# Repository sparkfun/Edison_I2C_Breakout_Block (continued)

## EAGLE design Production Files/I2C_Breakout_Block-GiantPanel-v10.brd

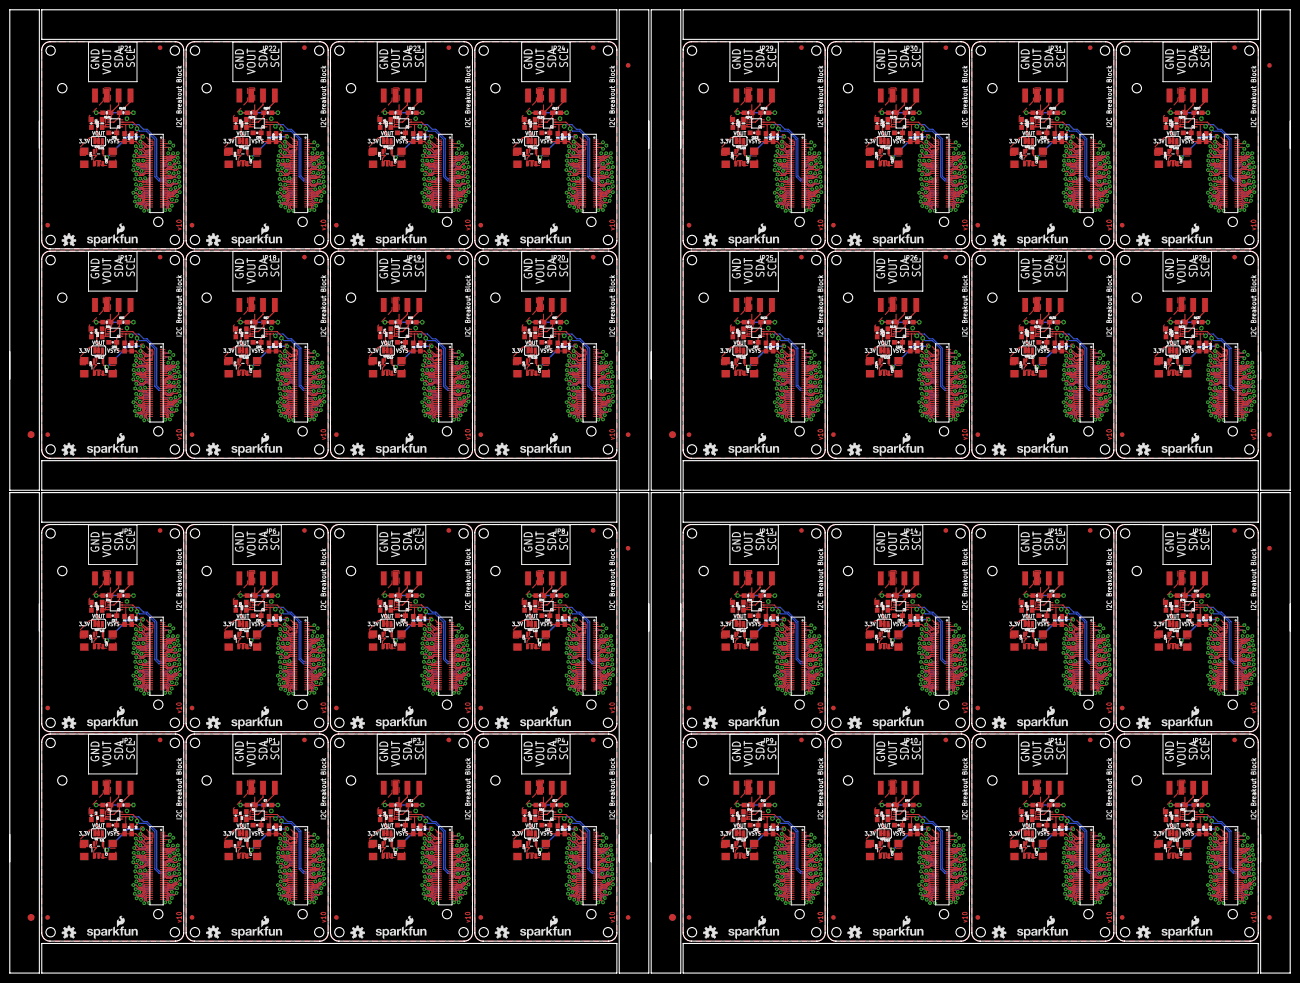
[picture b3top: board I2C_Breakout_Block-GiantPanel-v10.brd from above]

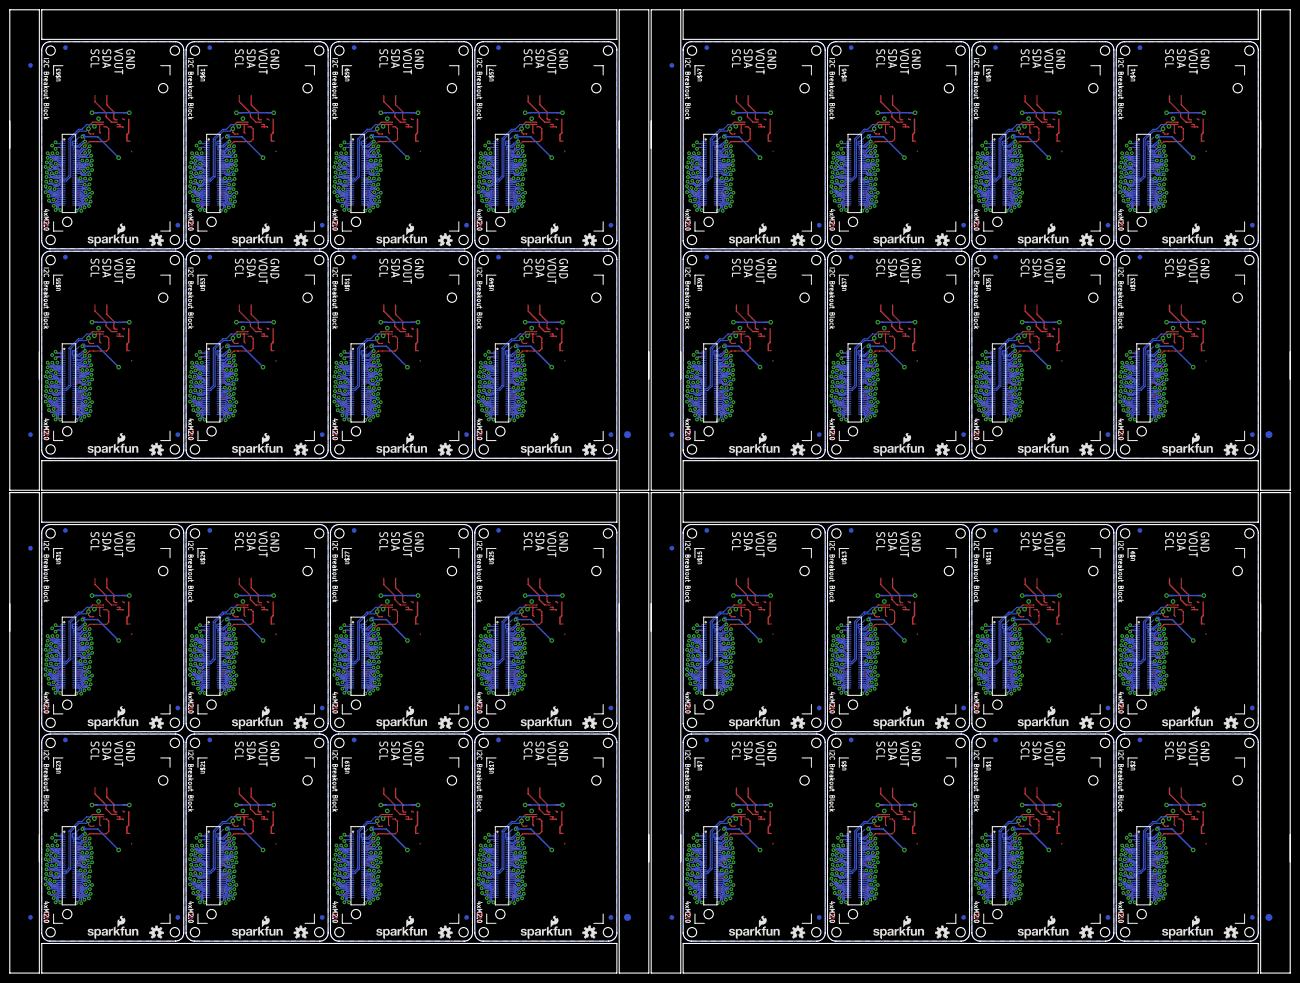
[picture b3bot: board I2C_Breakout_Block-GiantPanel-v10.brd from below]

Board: 2 copper layers, 274.8 x 206.8 mm, 760 parts (204 on the bottom side), 2016 nets.

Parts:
C1, C2, C5, C6, C9, C10, C13, C14, C17, C18, C21, C22, C25, C26, C29, C30, C33, C34, C37, C38, C41, C42, C45, C46, C49, C50, C53, C54, C57, C58, C61, C62, C65, C66, C69, C70, C73, C74, C77, C78, C81, C82, C85, C86, C89, C90, C93, C94, C97, C98, C101, C102, C105, C106, C109, C110, C113, C114, C117, C118, C121, C122, C125, C126: 0.1uF; 0603-CAP
C3, C4, C7, C8, C11, C12, C15, C16, C19, C20, C23, C24, C27, C28, C31, C32, C35, C36, C39, C40, C43, C44, C47, C48, C51, C52, C55, C56, C59, C60, C63, C64, C67, C68, C71, C72, C75, C76, C79, C80, C83, C84, C87, C88, C91, C92, C95, C96, C99, C100, C103, C104, C107, C108, C111, C112, C115, C116, C119, C120, C123, C124, C127, C128: 10uF; 1206
E$1, E$2, E$9, E$10, E$15, E$16, E$21, E$22: FIDUCIAL-1.5X3
E$3, E$4, E$5, E$6, E$7, E$8, E$11, E$12, E$13, E$14, E$17, E$18, E$19, E$20, E$23, E$24: FIDUCIAL-1X2
FID1, FID2, FID3, FID4, FID5, FID6, FID7, FID8, FID9, FID10, FID11, FID12, FID13, FID14, FID15, FID16, FID17, FID18, FID19, FID20, FID21, FID22, FID23, FID24, FID25, FID26, FID27, FID28, FID29, FID30, FID31, FID32, FID33, FID34, FID35, FID36, FID37, FID38, FID39, FID40, FID41, FID42, FID43, FID44, FID45, FID46, FID47, FID48, FID49, FID50, FID51, FID52, FID53, FID54, FID55, FID56, FID57, FID58, FID59, FID60, FID61, FID62, FID63, FID64, FID65, FID66, FID67, FID68, FID69, FID70, FID71, FID72, FID73, FID74, FID75, FID76, FID77, FID78, FID79, FID80, FID81, FID82, FID83, FID84, FID85, FID86, FID87, FID88, FID89, FID90, FID91, FID92, FID93, FID94, FID95, FID96, FID97, FID98, FID99, FID100, FID101, FID102, FID103, FID104, FID105, FID106, FID107, FID108, FID109, FID110, FID111, FID112, FID113, FID114, FID115, FID116, FID117, FID118, FID119, FID120, FID121, FID122, FID123, FID124, FID125, FID126, FID127, FID128: FIDUCIAL1X2; FIDUCIAL-1X2
JP1, JP2, JP3, JP4, JP5, JP6, JP7, JP8, JP9, JP10, JP11, JP12, JP13, JP14, JP15, JP16, JP17, JP18, JP19, JP20, JP21, JP22, JP23, JP24, JP25, JP26, JP27, JP28, JP29, JP30, JP31, JP32: 1X04_SMD_RA_FEMALE
LOGO1, LOGO3, LOGO6, LOGO7, LOGO10, LOGO11, LOGO14, LOGO15, LOGO18, LOGO19, LOGO22, LOGO23, LOGO26, LOGO27, LOGO30, LOGO31, LOGO34, LOGO35, LOGO38, LOGO39, LOGO42, LOGO43, LOGO46, LOGO47, LOGO50, LOGO51, LOGO54, LOGO55, LOGO58, LOGO59, LOGO62, LOGO63, LOGO66, LOGO67, LOGO70, LOGO71, LOGO74, LOGO75, LOGO78, LOGO79, LOGO82, LOGO83, LOGO86, LOGO87, LOGO90, LOGO91, LOGO94, LOGO95, LOGO98, LOGO99, LOGO102, LOGO103, LOGO106, LOGO107, LOGO110, LOGO111, LOGO114, LOGO115, LOGO118, LOGO119, LOGO122, LOGO123, LOGO126, LOGO127: SFE_LOGO_NAME_FLAME.1_INCH; SFE_LOGO_NAME_FLAME_.1
LOGO2, LOGO4, LOGO5, LOGO8, LOGO9, LOGO12, LOGO13, LOGO16, LOGO17, LOGO20, LOGO21, LOGO24, LOGO25, LOGO28, LOGO29, LOGO32, LOGO33, LOGO36, LOGO37, LOGO40, LOGO41, LOGO44, LOGO45, LOGO48, LOGO49, LOGO52, LOGO53, LOGO56, LOGO57, LOGO60, LOGO61, LOGO64, LOGO65, LOGO68, LOGO69, LOGO72, LOGO73, LOGO76, LOGO77, LOGO80, LOGO81, LOGO84, LOGO85, LOGO88, LOGO89, LOGO92, LOGO93, LOGO96, LOGO97, LOGO100, LOGO101, LOGO104, LOGO105, LOGO108, LOGO109, LOGO112, LOGO113, LOGO116, LOGO117, LOGO120, LOGO121, LOGO124, LOGO125, LOGO128: OSHW-LOGOS; OSHW-LOGO-S
R1, R2, R6, R7, R11, R12, R16, R17, R21, R22, R26, R27, R31, R32, R36, R37, R41, R42, R46, R47, R51, R52, R56, R57, R61, R62, R66, R67, R71, R72, R76, R77, R81, R82, R86, R87, R91, R92, R96, R97, R101, R102, R106, R107, R111, R112, R116, R117, R121, R122, R126, R127, R131, R132, R136, R137, R141, R142, R146, R147, R151, R152, R156, R157: 10K; 0603-RES
R3, R8, R13, R18, R23, R28, R33, R38, R43, R48, R53, R58, R63, R68, R73, R78, R83, R88, R93, R98, R103, R108, R113, R118, R123, R128, R133, R138, R143, R148, R153, R158: 200k; 0603-RES
R4, R5, R9, R10, R14, R15, R19, R20, R24, R25, R29, R30, R34, R35, R39, R40, R44, R45, R49, R50, R54, R55, R59, R60, R64, R65, R69, R70, R74, R75, R79, R80, R84, R85, R89, R90, R94, R95, R99, R100, R104, R105, R109, R110, R114, R115, R119, R120, R124, R125, R129, R130, R134, R135, R139, R140, R144, R145, R149, R150, R154, R155, R159, R160: DNP; 0603-RES
SJ1, SJ2, SJ3, SJ4, SJ5, SJ6, SJ7, SJ8, SJ9, SJ10, SJ11, SJ12, SJ13, SJ14, SJ15, SJ16, SJ17, SJ18, SJ19, SJ20, SJ21, SJ22, SJ23, SJ24, SJ25, SJ26, SJ27, SJ28, SJ29, SJ30, SJ31, SJ32: Power Select; PAD-JUMPER-3-2OF3_NC_BY_TRACE_YES_SILK_FULL_BOX
U1, U4, U6, U8, U10, U12, U14, U16, U18, U20, U22, U24, U26, U28, U30, U32, U34, U36, U38, U40, U42, U44, U46, U48, U50, U52, U54, U56, U58, U60, U62, U64: MIC5205; SOT23-5
U2, U3, U5, U7, U9, U11, U13, U15, U17, U19, U21, U23, U25, U27, U29, U31, U33, U35, U37, U39, U41, U43, U45, U47, U49, U51, U53, U55, U57, U59, U61, U63: PCA9306; PCA9306DC-1:1
U$1, U$2, U$5, U$7, U$9, U$11, U$13, U$15, U$17, U$19, U$21, U$23, U$25, U$27, U$29, U$31, U$33, U$35, U$37, U$39, U$41, U$43, U$45, U$47, U$49, U$51, U$53, U$55, U$57, U$59, U$61, U$63: EDISON_CONNECTOR_FULLMOUNTING_HOLES; EDISON_DAUGHTER
U$3, U$4, U$6, U$8, U$10, U$12, U$14, U$16, U$18, U$20, U$22, U$24, U$26, U$28, U$30, U$32, U$34, U$36, U$38, U$40, U$42, U$44, U$46, U$48, U$50, U$52, U$54, U$56, U$58, U$60, U$62, U$64: EDISON_CONNECTOR_FULLHEADER; DF40C-70DP-0.4(51)

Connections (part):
1.8V: C1.1, R4.2, R5.2, U2.1, U$2.12, U$3.12
1.8V1: C5.1, R9.2, R10.2, U3.1, U$1.12, U$4.12
1.8V2: C9.1, R14.2, R15.2, U5.1, U$5.12, U$6.12
1.8V3: C13.1, R19.2, R20.2, U7.1, U$7.12, U$8.12
1.8V4: C17.1, R24.2, R25.2, U9.1, U$9.12, U$10.12
1.8V5: C21.1, R29.2, R30.2, U11.1, U$11.12, U$12.12
1.8V6: C25.1, R34.2, R35.2, U13.1, U$13.12, U$14.12
1.8V7: C29.1, R39.2, R40.2, U15.1, U$15.12, U$16.12
1.8V8: C33.1, R44.2, R45.2, U17.1, U$17.12, U$18.12
1.8V9: C37.1, R49.2, R50.2, U19.1, U$19.12, U$20.12
1.8V10: C41.1, R54.2, R55.2, U21.1, U$21.12, U$22.12
1.8V11: C45.1, R59.2, R60.2, U23.1, U$23.12, U$24.12
1.8V12: C49.1, R64.2, R65.2, U25.1, U$25.12, U$26.12
1.8V13: C53.1, R69.2, R70.2, U27.1, U$27.12, U$28.12
1.8V14: C57.1, R74.2, R75.2, U29.1, U$29.12, U$30.12
1.8V15: C61.1, R79.2, R80.2, U31.1, U$31.12, U$32.12
1.8V16: C65.1, R84.2, R85.2, U33.1, U$33.12, U$34.12
1.8V17: C69.1, R89.2, R90.2, U35.1, U$35.12, U$36.12
1.8V18: C73.1, R94.2, R95.2, U37.1, U$37.12, U$38.12
1.8V19: C77.1, R99.2, R100.2, U39.1, U$39.12, U$40.12
1.8V20: C81.1, R104.2, R105.2, U41.1, U$41.12, U$42.12
1.8V21: C85.1, R109.2, R110.2, U43.1, U$43.12, U$44.12
1.8V22: C89.1, R114.2, R115.2, U45.1, U$45.12, U$46.12
1.8V23: C93.1, R119.2, R120.2, U47.1, U$47.12, U$48.12
1.8V24: C97.1, R124.2, R125.2, U49.1, U$49.12, U$50.12
1.8V25: C101.1, R129.2, R130.2, U51.1, U$51.12, U$52.12
1.8V26: C105.1, R134.2, R135.2, U53.1, U$53.12, U$54.12
1.8V27: C109.1, R139.2, R140.2, U55.1, U$55.12, U$56.12
1.8V28: C113.1, R144.2, R145.2, U57.1, U$57.12, U$58.12
1.8V29: C117.1, R149.2, R150.2, U59.1, U$59.12, U$60.12
1.8V30: C121.1, R154.2, R155.2, U61.1, U$61.12, U$62.12
1.8V31: C125.1, R159.2, R160.2, U63.1, U$63.12, U$64.12
3.3V: U$2.8, U$2.10, U$3.8, U$3.10
3.3V1: U$1.8, U$1.10, U$4.8, U$4.10
3.3V2: U$5.8, U$5.10, U$6.8, U$6.10
3.3V3: U$7.8, U$7.10, U$8.8, U$8.10
3.3V4: U$9.8, U$9.10, U$10.8, U$10.10
3.3V5: U$11.8, U$11.10, U$12.8, U$12.10
3.3V6: U$13.8, U$13.10, U$14.8, U$14.10
3.3V7: U$15.8, U$15.10, U$16.8, U$16.10
3.3V8: U$17.8, U$17.10, U$18.8, U$18.10
3.3V9: U$19.8, U$19.10, U$20.8, U$20.10
3.3V10: U$21.8, U$21.10, U$22.8, U$22.10
3.3V11: U$23.8, U$23.10, U$24.8, U$24.10
3.3V12: U$25.8, U$25.10, U$26.8, U$26.10
3.3V13: U$27.8, U$27.10, U$28.8, U$28.10
3.3V14: U$29.8, U$29.10, U$30.8, U$30.10
3.3V15: U$31.8, U$31.10, U$32.8, U$32.10
3.3V16: U$33.8, U$33.10, U$34.8, U$34.10
3.3V17: U$35.8, U$35.10, U$36.8, U$36.10
3.3V18: U$37.8, U$37.10, U$38.8, U$38.10
3.3V19: U$39.8, U$39.10, U$40.8, U$40.10
3.3V20: U$41.8, U$41.10, U$42.8, U$42.10
3.3V21: U$43.8, U$43.10, U$44.8, U$44.10
3.3V22: U$45.8, U$45.10, U$46.8, U$46.10
3.3V23: U$47.8, U$47.10, U$48.8, U$48.10
3.3V24: U$49.8, U$49.10, U$50.8, U$50.10
3.3V25: U$51.8, U$51.10, U$52.8, U$52.10
3.3V26: U$53.8, U$53.10, U$54.8, U$54.10
3.3V27: U$55.8, U$55.10, U$56.8, U$56.10
3.3V28: U$57.8, U$57.10, U$58.8, U$58.10
3.3V29: U$59.8, U$59.10, U$60.8, U$60.10
3.3V30: U$61.8, U$61.10, U$62.8, U$62.10
3.3V31: U$63.8, U$63.10, U$64.8, U$64.10
3.3V-REGULATED: C4.1, SJ1.3, U1.5
3.3V-REGULATED1: C8.1, SJ2.3, U4.5
3.3V-REGULATED2: C12.1, SJ3.3, U6.5
3.3V-REGULATED3: C16.1, SJ4.3, U8.5
3.3V-REGULATED4: C20.1, SJ5.3, U10.5
3.3V-REGULATED5: C24.1, SJ6.3, U12.5
3.3V-REGULATED6: C28.1, SJ7.3, U14.5
3.3V-REGULATED7: C32.1, SJ8.3, U16.5
3.3V-REGULATED8: C36.1, SJ9.3, U18.5
3.3V-REGULATED9: C40.1, SJ10.3, U20.5
3.3V-REGULATED10: C44.1, SJ11.3, U22.5
3.3V-REGULATED11: C48.1, SJ12.3, U24.5
3.3V-REGULATED12: C52.1, SJ13.3, U26.5
3.3V-REGULATED13: C56.1, SJ14.3, U28.5
3.3V-REGULATED14: C60.1, SJ15.3, U30.5
3.3V-REGULATED15: C64.1, SJ16.3, U32.5
3.3V-REGULATED16: C68.1, SJ17.3, U34.5
3.3V-REGULATED17: C72.1, SJ18.3, U36.5
3.3V-REGULATED18: C76.1, SJ19.3, U38.5
3.3V-REGULATED19: C80.1, SJ20.3, U40.5
3.3V-REGULATED20: C84.1, SJ21.3, U42.5
3.3V-REGULATED21: C88.1, SJ22.3, U44.5
3.3V-REGULATED22: C92.1, SJ23.3, U46.5
3.3V-REGULATED23: C96.1, SJ24.3, U48.5
3.3V-REGULATED24: C100.1, SJ25.3, U50.5
3.3V-REGULATED25: C104.1, SJ26.3, U52.5
3.3V-REGULATED26: C108.1, SJ27.3, U54.5
3.3V-REGULATED27: C112.1, SJ28.3, U56.5
3.3V-REGULATED28: C116.1, SJ29.3, U58.5
3.3V-REGULATED29: C120.1, SJ30.3, U60.5
3.3V-REGULATED30: C124.1, SJ31.3, U62.5
3.3V-REGULATED31: C128.1, SJ32.3, U64.5
DCIN: U$2.14, U$3.14
DCIN1: U$1.14, U$4.14
DCIN2: U$5.14, U$6.14
DCIN3: U$7.14, U$8.14
DCIN4: U$9.14, U$10.14
DCIN5: U$11.14, U$12.14
DCIN6: U$13.14, U$14.14
DCIN7: U$15.14, U$16.14
DCIN8: U$17.14, U$18.14
DCIN9: U$19.14, U$20.14
DCIN10: U$21.14, U$22.14
DCIN11: U$23.14, U$24.14
DCIN12: U$25.14, U$26.14
DCIN13: U$27.14, U$28.14
DCIN14: U$29.14, U$30.14
DCIN15: U$31.14, U$32.14
DCIN16: U$33.14, U$34.14
DCIN17: U$35.14, U$36.14
DCIN18: U$37.14, U$38.14
DCIN19: U$39.14, U$40.14
DCIN20: U$41.14, U$42.14
DCIN21: U$43.14, U$44.14
DCIN22: U$45.14, U$46.14
DCIN23: U$47.14, U$48.14
DCIN24: U$49.14, U$50.14
DCIN25: U$51.14, U$52.14
DCIN26: U$53.14, U$54.14
DCIN27: U$55.14, U$56.14
DCIN28: U$57.14, U$58.14
DCIN29: U$59.14, U$60.14
DCIN30: U$61.14, U$62.14
DCIN31: U$63.14, U$64.14
FAULT: U$2.19, U$3.19
FAULT1: U$1.19, U$4.19
FAULT2: U$5.19, U$6.19
FAULT3: U$7.19, U$8.19
FAULT4: U$9.19, U$10.19
FAULT5: U$11.19, U$12.19
FAULT6: U$13.19, U$14.19
FAULT7: U$15.19, U$16.19
FAULT8: U$17.19, U$18.19
FAULT9: U$19.19, U$20.19
FAULT10: U$21.19, U$22.19
FAULT11: U$23.19, U$24.19
FAULT12: U$25.19, U$26.19
FAULT13: U$27.19, U$28.19
FAULT14: U$29.19, U$30.19
FAULT15: U$31.19, U$32.19
FAULT16: U$33.19, U$34.19
FAULT17: U$35.19, U$36.19
FAULT18: U$37.19, U$38.19
FAULT19: U$39.19, U$40.19
FAULT20: U$41.19, U$42.19
FAULT21: U$43.19, U$44.19
FAULT22: U$45.19, U$46.19
FAULT23: U$47.19, U$48.19
FAULT24: U$49.19, U$50.19
FAULT25: U$51.19, U$52.19
FAULT26: U$53.19, U$54.19
FAULT27: U$55.19, U$56.19
FAULT28: U$57.19, U$58.19
FAULT29: U$59.19, U$60.19
FAULT30: U$61.19, U$62.19
FAULT31: U$63.19, U$64.19
FW_RCVR: U$2.69, U$3.69
FW_RCVR1: U$1.69, U$4.69
FW_RCVR2: U$5.69, U$6.69
FW_RCVR3: U$7.69, U$8.69
FW_RCVR4: U$9.69, U$10.69
FW_RCVR5: U$11.69, U$12.69
FW_RCVR6: U$13.69, U$14.69
FW_RCVR7: U$15.69, U$16.69
FW_RCVR8: U$17.69, U$18.69
FW_RCVR9: U$19.69, U$20.69
FW_RCVR10: U$21.69, U$22.69
FW_RCVR11: U$23.69, U$24.69
FW_RCVR12: U$25.69, U$26.69
FW_RCVR13: U$27.69, U$28.69
FW_RCVR14: U$29.69, U$30.69
FW_RCVR15: U$31.69, U$32.69
FW_RCVR16: U$33.69, U$34.69
FW_RCVR17: U$35.69, U$36.69
FW_RCVR18: U$37.69, U$38.69
FW_RCVR19: U$39.69, U$40.69
FW_RCVR20: U$41.69, U$42.69
FW_RCVR21: U$43.69, U$44.69
FW_RCVR22: U$45.69, U$46.69
FW_RCVR23: U$47.69, U$48.69
FW_RCVR24: U$49.69, U$50.69
FW_RCVR25: U$51.69, U$52.69
FW_RCVR26: U$53.69, U$54.69
FW_RCVR27: U$55.69, U$56.69
FW_RCVR28: U$57.69, U$58.69
FW_RCVR29: U$59.69, U$60.69
FW_RCVR30: U$61.69, U$62.69
FW_RCVR31: U$63.69, U$64.69
GND: C1.2, C2.2, C3.2, C4.2, JP2.4, U1.2, U2.4, U$2.1, U$2.5, U$2.9, U$2.11, U$2.13, U$2.15, U$3.1, U$3.5, U$3.9, U$3.11, U$3.13, U$3.15
GND1: C5.2, C6.2, C7.2, C8.2, JP1.4, U3.4, U4.2, U$1.1, U$1.5, U$1.9, U$1.11, U$1.13, U$1.15, U$4.1, U$4.5, U$4.9, U$4.11, U$4.13, U$4.15
GND2: C9.2, C10.2, C11.2, C12.2, JP3.4, U5.4, U6.2, U$5.1, U$5.5, U$5.9, U$5.11, U$5.13, U$5.15, U$6.1, U$6.5, U$6.9, U$6.11, U$6.13, U$6.15
GND3: C13.2, C14.2, C15.2, C16.2, JP4.4, U7.4, U8.2, U$7.1, U$7.5, U$7.9, U$7.11, U$7.13, U$7.15, U$8.1, U$8.5, U$8.9, U$8.11, U$8.13, U$8.15
GND4: C17.2, C18.2, C19.2, C20.2, JP5.4, U9.4, U10.2, U$9.1, U$9.5, U$9.9, U$9.11, U$9.13, U$9.15, U$10.1, U$10.5, U$10.9, U$10.11, U$10.13, U$10.15
GND5: C21.2, C22.2, C23.2, C24.2, JP6.4, U11.4, U12.2, U$11.1, U$11.5, U$11.9, U$11.11, U$11.13, U$11.15, U$12.1, U$12.5, U$12.9, U$12.11, U$12.13, U$12.15
GND6: C25.2, C26.2, C27.2, C28.2, JP7.4, U13.4, U14.2, U$13.1, U$13.5, U$13.9, U$13.11, U$13.13, U$13.15, U$14.1, U$14.5, U$14.9, U$14.11, U$14.13, U$14.15
GND7: C29.2, C30.2, C31.2, C32.2, JP8.4, U15.4, U16.2, U$15.1, U$15.5, U$15.9, U$15.11, U$15.13, U$15.15, U$16.1, U$16.5, U$16.9, U$16.11, U$16.13, U$16.15
GND8: C33.2, C34.2, C35.2, C36.2, JP9.4, U17.4, U18.2, U$17.1, U$17.5, U$17.9, U$17.11, U$17.13, U$17.15, U$18.1, U$18.5, U$18.9, U$18.11, U$18.13, U$18.15
GND9: C37.2, C38.2, C39.2, C40.2, JP10.4, U19.4, U20.2, U$19.1, U$19.5, U$19.9, U$19.11, U$19.13, U$19.15, U$20.1, U$20.5, U$20.9, U$20.11, U$20.13, U$20.15
GND10: C41.2, C42.2, C43.2, C44.2, JP11.4, U21.4, U22.2, U$21.1, U$21.5, U$21.9, U$21.11, U$21.13, U$21.15, U$22.1, U$22.5, U$22.9, U$22.11, U$22.13, U$22.15
GND11: C45.2, C46.2, C47.2, C48.2, JP12.4, U23.4, U24.2, U$23.1, U$23.5, U$23.9, U$23.11, U$23.13, U$23.15, U$24.1, U$24.5, U$24.9, U$24.11, U$24.13, U$24.15
GND12: C49.2, C50.2, C51.2, C52.2, JP13.4, U25.4, U26.2, U$25.1, U$25.5, U$25.9, U$25.11, U$25.13, U$25.15, U$26.1, U$26.5, U$26.9, U$26.11, U$26.13, U$26.15
GND13: C53.2, C54.2, C55.2, C56.2, JP14.4, U27.4, U28.2, U$27.1, U$27.5, U$27.9, U$27.11, U$27.13, U$27.15, U$28.1, U$28.5, U$28.9, U$28.11, U$28.13, U$28.15
GND14: C57.2, C58.2, C59.2, C60.2, JP15.4, U29.4, U30.2, U$29.1, U$29.5, U$29.9, U$29.11, U$29.13, U$29.15, U$30.1, U$30.5, U$30.9, U$30.11, U$30.13, U$30.15
GND15: C61.2, C62.2, C63.2, C64.2, JP16.4, U31.4, U32.2, U$31.1, U$31.5, U$31.9, U$31.11, U$31.13, U$31.15, U$32.1, U$32.5, U$32.9, U$32.11, U$32.13, U$32.15
GND16: C65.2, C66.2, C67.2, C68.2, JP17.4, U33.4, U34.2, U$33.1, U$33.5, U$33.9, U$33.11, U$33.13, U$33.15, U$34.1, U$34.5, U$34.9, U$34.11, U$34.13, U$34.15
GND17: C69.2, C70.2, C71.2, C72.2, JP18.4, U35.4, U36.2, U$35.1, U$35.5, U$35.9, U$35.11, U$35.13, U$35.15, U$36.1, U$36.5, U$36.9, U$36.11, U$36.13, U$36.15
GND18: C73.2, C74.2, C75.2, C76.2, JP19.4, U37.4, U38.2, U$37.1, U$37.5, U$37.9, U$37.11, U$37.13, U$37.15, U$38.1, U$38.5, U$38.9, U$38.11, U$38.13, U$38.15
GND19: C77.2, C78.2, C79.2, C80.2, JP20.4, U39.4, U40.2, U$39.1, U$39.5, U$39.9, U$39.11, U$39.13, U$39.15, U$40.1, U$40.5, U$40.9, U$40.11, U$40.13, U$40.15
GND20: C81.2, C82.2, C83.2, C84.2, JP21.4, U41.4, U42.2, U$41.1, U$41.5, U$41.9, U$41.11, U$41.13, U$41.15, U$42.1, U$42.5, U$42.9, U$42.11, U$42.13, U$42.15
GND21: C85.2, C86.2, C87.2, C88.2, JP22.4, U43.4, U44.2, U$43.1, U$43.5, U$43.9, U$43.11, U$43.13, U$43.15, U$44.1, U$44.5, U$44.9, U$44.11, U$44.13, U$44.15
GND22: C89.2, C90.2, C91.2, C92.2, JP23.4, U45.4, U46.2, U$45.1, U$45.5, U$45.9, U$45.11, U$45.13, U$45.15, U$46.1, U$46.5, U$46.9, U$46.11, U$46.13, U$46.15
GND23: C93.2, C94.2, C95.2, C96.2, JP24.4, U47.4, U48.2, U$47.1, U$47.5, U$47.9, U$47.11, U$47.13, U$47.15, U$48.1, U$48.5, U$48.9, U$48.11, U$48.13, U$48.15
GND24: C97.2, C98.2, C99.2, C100.2, JP25.4, U49.4, U50.2, U$49.1, U$49.5, U$49.9, U$49.11, U$49.13, U$49.15, U$50.1, U$50.5, U$50.9, U$50.11, U$50.13, U$50.15
GND25: C101.2, C102.2, C103.2, C104.2, JP26.4, U51.4, U52.2, U$51.1, U$51.5, U$51.9, U$51.11, U$51.13, U$51.15, U$52.1, U$52.5, U$52.9, U$52.11, U$52.13, U$52.15
GND26: C105.2, C106.2, C107.2, C108.2, JP27.4, U53.4, U54.2, U$53.1, U$53.5, U$53.9, U$53.11, U$53.13, U$53.15, U$54.1, U$54.5, U$54.9, U$54.11, U$54.13, U$54.15
GND27: C109.2, C110.2, C111.2, C112.2, JP28.4, U55.4, U56.2, U$55.1, U$55.5, U$55.9, U$55.11, U$55.13, U$55.15, U$56.1, U$56.5, U$56.9, U$56.11, U$56.13, U$56.15
GND28: C113.2, C114.2, C115.2, C116.2, JP29.4, U57.4, U58.2, U$57.1, U$57.5, U$57.9, U$57.11, U$57.13, U$57.15, U$58.1, U$58.5, U$58.9, U$58.11, U$58.13, U$58.15
GND29: C117.2, C118.2, C119.2, C120.2, JP30.4, U59.4, U60.2, U$59.1, U$59.5, U$59.9, U$59.11, U$59.13, U$59.15, U$60.1, U$60.5, U$60.9, U$60.11, U$60.13, U$60.15
GND30: C121.2, C122.2, C123.2, C124.2, JP31.4, U61.4, U62.2, U$61.1, U$61.5, U$61.9, U$61.11, U$61.13, U$61.15, U$62.1, U$62.5, U$62.9, U$62.11, U$62.13, U$62.15
GND31: C125.2, C126.2, C127.2, C128.2, JP32.4, U63.4, U64.2, U$63.1, U$63.5, U$63.9, U$63.11, U$63.13, U$63.15, U$64.1, U$64.5, U$64.9, U$64.11, U$64.13, U$64.15
GP1: U$1.48, U$4.48
GP2: U$1.42, U$4.42
GP3: U$1.34, U$4.34
GP4: U$1.32, U$4.32
GP5: U$1.30, U$4.30
GP6: U$1.28, U$4.28
GP7: U$1.26, U$4.26
GP8: U$1.25, U$4.25
GP9: U$1.24, U$4.24
GP10: U$5.48, U$6.48
GP11: U$5.42, U$6.42
GP12: U$5.34, U$6.34
GP12_PWM0: U$2.35, U$3.35
GP12_PWM1: U$1.35, U$4.35
GP12_PWM2: U$5.35, U$6.35
GP12_PWM3: U$7.35, U$8.35
GP12_PWM4: U$9.35, U$10.35
GP12_PWM5: U$11.35, U$12.35
GP12_PWM6: U$13.35, U$14.35
GP12_PWM7: U$15.35, U$16.35
GP12_PWM8: U$17.35, U$18.35
GP12_PWM9: U$19.35, U$20.35
GP12_PWM10: U$21.35, U$22.35
GP12_PWM11: U$23.35, U$24.35
GP12_PWM12: U$25.35, U$26.35
GP12_PWM13: U$27.35, U$28.35
GP12_PWM14: U$29.35, U$30.35
GP12_PWM15: U$31.35, U$32.35
GP12_PWM16: U$33.35, U$34.35
GP12_PWM17: U$35.35, U$36.35
GP12_PWM18: U$37.35, U$38.35
GP12_PWM19: U$39.35, U$40.35
GP12_PWM20: U$41.35, U$42.35
GP12_PWM21: U$43.35, U$44.35
GP12_PWM22: U$45.35, U$46.35
GP12_PWM23: U$47.35, U$48.35
GP12_PWM24: U$49.35, U$50.35
GP12_PWM25: U$51.35, U$52.35
GP12_PWM26: U$53.35, U$54.35
GP12_PWM27: U$55.35, U$56.35
GP12_PWM28: U$57.35, U$58.35
GP12_PWM29: U$59.35, U$60.35
GP12_PWM30: U$61.35, U$62.35
GP12_PWM31: U$63.35, U$64.35
GP13: U$5.32, U$6.32
GP13_PWM1: U$2.33, U$3.33
GP13_PWM2: U$1.33, U$4.33
GP13_PWM3: U$5.33, U$6.33
GP13_PWM4: U$7.33, U$8.33
GP13_PWM5: U$9.33, U$10.33
GP13_PWM6: U$11.33, U$12.33
GP13_PWM7: U$13.33, U$14.33
GP13_PWM8: U$15.33, U$16.33
GP13_PWM9: U$17.33, U$18.33
GP13_PWM10: U$19.33, U$20.33
GP13_PWM11: U$21.33, U$22.33
GP13_PWM12: U$23.33, U$24.33
GP13_PWM13: U$25.33, U$26.33
GP13_PWM14: U$27.33, U$28.33
GP13_PWM15: U$29.33, U$30.33
GP13_PWM16: U$31.33, U$32.33
GP13_PWM17: U$33.33, U$34.33
GP13_PWM18: U$35.33, U$36.33
GP13_PWM19: U$37.33, U$38.33
GP13_PWM20: U$39.33, U$40.33
GP13_PWM21: U$41.33, U$42.33
GP13_PWM22: U$43.33, U$44.33
GP13_PWM23: U$45.33, U$46.33
GP13_PWM24: U$47.33, U$48.33
GP13_PWM25: U$49.33, U$50.33
GP13_PWM26: U$51.33, U$52.33
GP13_PWM27: U$53.33, U$54.33
GP13_PWM28: U$55.33, U$56.33
GP13_PWM29: U$57.33, U$58.33
GP13_PWM30: U$59.33, U$60.33
GP13_PWM31: U$61.33, U$62.33
GP13_PWM32: U$63.33, U$64.33
GP14: U$2.48, U$3.48
GP15: U$2.42, U$3.42
GP16: U$5.30, U$6.30
GP17: U$5.28, U$6.28
GP18: U$5.26, U$6.26
GP19: U$5.25, U$6.25
GP19_I2C_1_SCL: R4.1, U2.2, U$2.41, U$3.41
GP19_I2C_1_SCL1: R9.1, U3.2, U$1.41, U$4.41
GP19_I2C_1_SCL2: R14.1, U5.2, U$5.41, U$6.41
GP19_I2C_1_SCL3: R19.1, U7.2, U$7.41, U$8.41
GP19_I2C_1_SCL4: R24.1, U9.2, U$9.41, U$10.41
GP19_I2C_1_SCL5: R29.1, U11.2, U$11.41, U$12.41
GP19_I2C_1_SCL6: R34.1, U13.2, U$13.41, U$14.41
GP19_I2C_1_SCL7: R39.1, U15.2, U$15.41, U$16.41
GP19_I2C_1_SCL8: R44.1, U17.2, U$17.41, U$18.41
GP19_I2C_1_SCL9: R49.1, U19.2, U$19.41, U$20.41
GP19_I2C_1_SCL10: R54.1, U21.2, U$21.41, U$22.41
GP19_I2C_1_SCL11: R59.1, U23.2, U$23.41, U$24.41
GP19_I2C_1_SCL12: R64.1, U25.2, U$25.41, U$26.41
GP19_I2C_1_SCL13: R69.1, U27.2, U$27.41, U$28.41
GP19_I2C_1_SCL14: R74.1, U29.2, U$29.41, U$30.41
GP19_I2C_1_SCL15: R79.1, U31.2, U$31.41, U$32.41
GP19_I2C_1_SCL16: R84.1, U33.2, U$33.41, U$34.41
GP19_I2C_1_SCL17: R89.1, U35.2, U$35.41, U$36.41
GP19_I2C_1_SCL18: R94.1, U37.2, U$37.41, U$38.41
GP19_I2C_1_SCL19: R99.1, U39.2, U$39.41, U$40.41
GP19_I2C_1_SCL20: R104.1, U41.2, U$41.41, U$42.41
GP19_I2C_1_SCL21: R109.1, U43.2, U$43.41, U$44.41
GP19_I2C_1_SCL22: R114.1, U45.2, U$45.41, U$46.41
GP19_I2C_1_SCL23: R119.1, U47.2, U$47.41, U$48.41
GP19_I2C_1_SCL24: R124.1, U49.2, U$49.41, U$50.41
GP19_I2C_1_SCL25: R129.1, U51.2, U$51.41, U$52.41
GP19_I2C_1_SCL26: R134.1, U53.2, U$53.41, U$54.41
GP19_I2C_1_SCL27: R139.1, U55.2, U$55.41, U$56.41
GP19_I2C_1_SCL28: R144.1, U57.2, U$57.41, U$58.41
GP19_I2C_1_SCL29: R149.1, U59.2, U$59.41, U$60.41
GP19_I2C_1_SCL30: R154.1, U61.2, U$61.41, U$62.41
GP19_I2C_1_SCL31: R159.1, U63.2, U$63.41, U$64.41
GP20: U$5.24, U$6.24
GP20_I2C_1_SDA: R5.1, U2.3, U$2.43, U$3.43
GP20_I2C_1_SDA1: R10.1, U3.3, U$1.43, U$4.43
GP20_I2C_1_SDA2: R15.1, U5.3, U$5.43, U$6.43
GP20_I2C_1_SDA3: R20.1, U7.3, U$7.43, U$8.43
GP20_I2C_1_SDA4: R25.1, U9.3, U$9.43, U$10.43
GP20_I2C_1_SDA5: R30.1, U11.3, U$11.43, U$12.43
GP20_I2C_1_SDA6: R35.1, U13.3, U$13.43, U$14.43
GP20_I2C_1_SDA7: R40.1, U15.3, U$15.43, U$16.43
GP20_I2C_1_SDA8: R45.1, U17.3, U$17.43, U$18.43
GP20_I2C_1_SDA9: R50.1, U19.3, U$19.43, U$20.43
GP20_I2C_1_SDA10: R55.1, U21.3, U$21.43, U$22.43
GP20_I2C_1_SDA11: R60.1, U23.3, U$23.43, U$24.43
GP20_I2C_1_SDA12: R65.1, U25.3, U$25.43, U$26.43
GP20_I2C_1_SDA13: R70.1, U27.3, U$27.43, U$28.43
GP20_I2C_1_SDA14: R75.1, U29.3, U$29.43, U$30.43
GP20_I2C_1_SDA15: R80.1, U31.3, U$31.43, U$32.43
GP20_I2C_1_SDA16: R85.1, U33.3, U$33.43, U$34.43
GP20_I2C_1_SDA17: R90.1, U35.3, U$35.43, U$36.43
GP20_I2C_1_SDA18: R95.1, U37.3, U$37.43, U$38.43
GP20_I2C_1_SDA19: R100.1, U39.3, U$39.43, U$40.43
GP20_I2C_1_SDA20: R105.1, U41.3, U$41.43, U$42.43
GP20_I2C_1_SDA21: R110.1, U43.3, U$43.43, U$44.43
GP20_I2C_1_SDA22: R115.1, U45.3, U$45.43, U$46.43
GP20_I2C_1_SDA23: R120.1, U47.3, U$47.43, U$48.43
GP20_I2C_1_SDA24: R125.1, U49.3, U$49.43, U$50.43
GP20_I2C_1_SDA25: R130.1, U51.3, U$51.43, U$52.43
GP20_I2C_1_SDA26: R135.1, U53.3, U$53.43, U$54.43
GP20_I2C_1_SDA27: R140.1, U55.3, U$55.43, U$56.43
GP20_I2C_1_SDA28: R145.1, U57.3, U$57.43, U$58.43
GP20_I2C_1_SDA29: R150.1, U59.3, U$59.43, U$60.43
GP20_I2C_1_SDA30: R155.1, U61.3, U$61.43, U$62.43
GP20_I2C_1_SDA31: R160.1, U63.3, U$63.43, U$64.43
GP21: U$7.48, U$8.48
GP22: U$7.42, U$8.42
GP23: U$7.34, U$8.34
GP24: U$7.32, U$8.32
GP25: U$7.30, U$8.30
GP26: U$7.28, U$8.28
GP27: U$7.26, U$8.26
GP27_I2C_6_SCL: U$2.45, U$3.45
GP27_I2C_6_SCL1: U$1.45, U$4.45
GP27_I2C_6_SCL2: U$5.45, U$6.45
GP27_I2C_6_SCL3: U$7.45, U$8.45
GP27_I2C_6_SCL4: U$9.45, U$10.45
GP27_I2C_6_SCL5: U$11.45, U$12.45
GP27_I2C_6_SCL6: U$13.45, U$14.45
GP27_I2C_6_SCL7: U$15.45, U$16.45
GP27_I2C_6_SCL8: U$17.45, U$18.45
GP27_I2C_6_SCL9: U$19.45, U$20.45
GP27_I2C_6_SCL10: U$21.45, U$22.45
GP27_I2C_6_SCL11: U$23.45, U$24.45
GP27_I2C_6_SCL12: U$25.45, U$26.45
GP27_I2C_6_SCL13: U$27.45, U$28.45
GP27_I2C_6_SCL14: U$29.45, U$30.45
GP27_I2C_6_SCL15: U$31.45, U$32.45
GP27_I2C_6_SCL16: U$33.45, U$34.45
GP27_I2C_6_SCL17: U$35.45, U$36.45
GP27_I2C_6_SCL18: U$37.45, U$38.45
GP27_I2C_6_SCL19: U$39.45, U$40.45
GP27_I2C_6_SCL20: U$41.45, U$42.45
GP27_I2C_6_SCL21: U$43.45, U$44.45
GP27_I2C_6_SCL22: U$45.45, U$46.45
GP27_I2C_6_SCL23: U$47.45, U$48.45
GP27_I2C_6_SCL24: U$49.45, U$50.45
GP27_I2C_6_SCL25: U$51.45, U$52.45
GP27_I2C_6_SCL26: U$53.45, U$54.45
GP27_I2C_6_SCL27: U$55.45, U$56.45
GP27_I2C_6_SCL28: U$57.45, U$58.45
GP27_I2C_6_SCL29: U$59.45, U$60.45
GP27_I2C_6_SCL30: U$61.45, U$62.45
GP27_I2C_6_SCL31: U$63.45, U$64.45
GP28: U$7.25, U$8.25
GP28_I2C_6_SDA: U$2.47, U$3.47
GP28_I2C_6_SDA1: U$1.47, U$4.47
GP28_I2C_6_SDA2: U$5.47, U$6.47
GP28_I2C_6_SDA3: U$7.47, U$8.47
GP28_I2C_6_SDA4: U$9.47, U$10.47
GP28_I2C_6_SDA5: U$11.47, U$12.47
GP28_I2C_6_SDA6: U$13.47, U$14.47
GP28_I2C_6_SDA7: U$15.47, U$16.47
GP28_I2C_6_SDA8: U$17.47, U$18.47
GP28_I2C_6_SDA9: U$19.47, U$20.47
GP28_I2C_6_SDA10: U$21.47, U$22.47
GP28_I2C_6_SDA11: U$23.47, U$24.47
GP28_I2C_6_SDA12: U$25.47, U$26.47
GP28_I2C_6_SDA13: U$27.47, U$28.47
GP28_I2C_6_SDA14: U$29.47, U$30.47
GP28_I2C_6_SDA15: U$31.47, U$32.47
GP28_I2C_6_SDA16: U$33.47, U$34.47
GP28_I2C_6_SDA17: U$35.47, U$36.47
GP28_I2C_6_SDA18: U$37.47, U$38.47
GP28_I2C_6_SDA19: U$39.47, U$40.47
GP28_I2C_6_SDA20: U$41.47, U$42.47
GP28_I2C_6_SDA21: U$43.47, U$44.47
GP28_I2C_6_SDA22: U$45.47, U$46.47
GP28_I2C_6_SDA23: U$47.47, U$48.47
GP28_I2C_6_SDA24: U$49.47, U$50.47
GP28_I2C_6_SDA25: U$51.47, U$52.47
GP28_I2C_6_SDA26: U$53.47, U$54.47
GP28_I2C_6_SDA27: U$55.47, U$56.47
GP28_I2C_6_SDA28: U$57.47, U$58.47
GP28_I2C_6_SDA29: U$59.47, U$60.47
GP28_I2C_6_SDA30: U$61.47, U$62.47
GP28_I2C_6_SDA31: U$63.47, U$64.47
GP29: U$7.24, U$8.24
GP30: U$9.48, U$10.48
GP31: U$9.42, U$10.42
GP32: U$9.34, U$10.34
GP33: U$9.32, U$10.32
GP34: U$9.30, U$10.30
GP35: U$9.28, U$10.28
GP36: U$9.26, U$10.26
GP37: U$9.25, U$10.25
GP38: U$9.24, U$10.24
GP39: U$11.48, U$12.48
GP40: U$11.42, U$12.42
GP40_I2S_2_CLK: U$2.52, U$3.52
GP40_I2S_2_CLK1: U$1.52, U$4.52
GP40_I2S_2_CLK2: U$5.52, U$6.52
GP40_I2S_2_CLK3: U$7.52, U$8.52
GP40_I2S_2_CLK4: U$9.52, U$10.52
GP40_I2S_2_CLK5: U$11.52, U$12.52
GP40_I2S_2_CLK6: U$13.52, U$14.52
GP40_I2S_2_CLK7: U$15.52, U$16.52
GP40_I2S_2_CLK8: U$17.52, U$18.52
GP40_I2S_2_CLK9: U$19.52, U$20.52
GP40_I2S_2_CLK10: U$21.52, U$22.52
GP40_I2S_2_CLK11: U$23.52, U$24.52
GP40_I2S_2_CLK12: U$25.52, U$26.52
GP40_I2S_2_CLK13: U$27.52, U$28.52
GP40_I2S_2_CLK14: U$29.52, U$30.52
GP40_I2S_2_CLK15: U$31.52, U$32.52
GP40_I2S_2_CLK16: U$33.52, U$34.52
GP40_I2S_2_CLK17: U$35.52, U$36.52
GP40_I2S_2_CLK18: U$37.52, U$38.52
GP40_I2S_2_CLK19: U$39.52, U$40.52
GP40_I2S_2_CLK20: U$41.52, U$42.52
GP40_I2S_2_CLK21: U$43.52, U$44.52
GP40_I2S_2_CLK22: U$45.52, U$46.52
GP40_I2S_2_CLK23: U$47.52, U$48.52
GP40_I2S_2_CLK24: U$49.52, U$50.52
GP40_I2S_2_CLK25: U$51.52, U$52.52
GP40_I2S_2_CLK26: U$53.52, U$54.52
GP40_I2S_2_CLK27: U$55.52, U$56.52
GP40_I2S_2_CLK28: U$57.52, U$58.52
GP40_I2S_2_CLK29: U$59.52, U$60.52
GP40_I2S_2_CLK30: U$61.52, U$62.52
GP40_I2S_2_CLK31: U$63.52, U$64.52
GP41: U$11.34, U$12.34
GP41_I2S_2_FS: U$2.54, U$3.54
GP41_I2S_2_FS1: U$1.54, U$4.54
GP41_I2S_2_FS2: U$5.54, U$6.54
GP41_I2S_2_FS3: U$7.54, U$8.54
GP41_I2S_2_FS4: U$9.54, U$10.54
GP41_I2S_2_FS5: U$11.54, U$12.54
GP41_I2S_2_FS6: U$13.54, U$14.54
GP41_I2S_2_FS7: U$15.54, U$16.54
GP41_I2S_2_FS8: U$17.54, U$18.54
GP41_I2S_2_FS9: U$19.54, U$20.54
GP41_I2S_2_FS10: U$21.54, U$22.54
GP41_I2S_2_FS11: U$23.54, U$24.54
GP41_I2S_2_FS12: U$25.54, U$26.54
GP41_I2S_2_FS13: U$27.54, U$28.54
GP41_I2S_2_FS14: U$29.54, U$30.54
GP41_I2S_2_FS15: U$31.54, U$32.54
GP41_I2S_2_FS16: U$33.54, U$34.54
GP41_I2S_2_FS17: U$35.54, U$36.54
GP41_I2S_2_FS18: U$37.54, U$38.54
GP41_I2S_2_FS19: U$39.54, U$40.54
GP41_I2S_2_FS20: U$41.54, U$42.54
GP41_I2S_2_FS21: U$43.54, U$44.54
GP41_I2S_2_FS22: U$45.54, U$46.54
GP41_I2S_2_FS23: U$47.54, U$48.54
GP41_I2S_2_FS24: U$49.54, U$50.54
GP41_I2S_2_FS25: U$51.54, U$52.54
GP41_I2S_2_FS26: U$53.54, U$54.54
GP41_I2S_2_FS27: U$55.54, U$56.54
GP41_I2S_2_FS28: U$57.54, U$58.54
GP41_I2S_2_FS29: U$59.54, U$60.54
GP41_I2S_2_FS30: U$61.54, U$62.54
GP41_I2S_2_FS31: U$63.54, U$64.54
GP42: U$11.32, U$12.32
GP42_I2S_2_RXD: U$2.50, U$3.50
GP42_I2S_2_RXD1: U$1.50, U$4.50
GP42_I2S_2_RXD2: U$5.50, U$6.50
GP42_I2S_2_RXD3: U$7.50, U$8.50
GP42_I2S_2_RXD4: U$9.50, U$10.50
GP42_I2S_2_RXD5: U$11.50, U$12.50
GP42_I2S_2_RXD6: U$13.50, U$14.50
GP42_I2S_2_RXD7: U$15.50, U$16.50
GP42_I2S_2_RXD8: U$17.50, U$18.50
GP42_I2S_2_RXD9: U$19.50, U$20.50
GP42_I2S_2_RXD10: U$21.50, U$22.50
GP42_I2S_2_RXD11: U$23.50, U$24.50
GP42_I2S_2_RXD12: U$25.50, U$26.50
GP42_I2S_2_RXD13: U$27.50, U$28.50
GP42_I2S_2_RXD14: U$29.50, U$30.50
GP42_I2S_2_RXD15: U$31.50, U$32.50
GP42_I2S_2_RXD16: U$33.50, U$34.50
GP42_I2S_2_RXD17: U$35.50, U$36.50
GP42_I2S_2_RXD18: U$37.50, U$38.50
GP42_I2S_2_RXD19: U$39.50, U$40.50
GP42_I2S_2_RXD20: U$41.50, U$42.50
GP42_I2S_2_RXD21: U$43.50, U$44.50
GP42_I2S_2_RXD22: U$45.50, U$46.50
GP42_I2S_2_RXD23: U$47.50, U$48.50
GP42_I2S_2_RXD24: U$49.50, U$50.50
GP42_I2S_2_RXD25: U$51.50, U$52.50
GP42_I2S_2_RXD26: U$53.50, U$54.50
GP42_I2S_2_RXD27: U$55.50, U$56.50
GP42_I2S_2_RXD28: U$57.50, U$58.50
GP42_I2S_2_RXD29: U$59.50, U$60.50
GP42_I2S_2_RXD30: U$61.50, U$62.50
GP42_I2S_2_RXD31: U$63.50, U$64.50
GP43: U$11.30, U$12.30
GP43_I2S_2_TXD: U$2.56, U$3.56
GP43_I2S_2_TXD1: U$1.56, U$4.56
GP43_I2S_2_TXD2: U$5.56, U$6.56
GP43_I2S_2_TXD3: U$7.56, U$8.56
GP43_I2S_2_TXD4: U$9.56, U$10.56
GP43_I2S_2_TXD5: U$11.56, U$12.56
GP43_I2S_2_TXD6: U$13.56, U$14.56
GP43_I2S_2_TXD7: U$15.56, U$16.56
GP43_I2S_2_TXD8: U$17.56, U$18.56
GP43_I2S_2_TXD9: U$19.56, U$20.56
GP43_I2S_2_TXD10: U$21.56, U$22.56
GP43_I2S_2_TXD11: U$23.56, U$24.56
GP43_I2S_2_TXD12: U$25.56, U$26.56
GP43_I2S_2_TXD13: U$27.56, U$28.56
GP43_I2S_2_TXD14: U$29.56, U$30.56
GP43_I2S_2_TXD15: U$31.56, U$32.56
GP43_I2S_2_TXD16: U$33.56, U$34.56
GP43_I2S_2_TXD17: U$35.56, U$36.56
GP43_I2S_2_TXD18: U$37.56, U$38.56
GP43_I2S_2_TXD19: U$39.56, U$40.56
GP43_I2S_2_TXD20: U$41.56, U$42.56
GP43_I2S_2_TXD21: U$43.56, U$44.56
GP43_I2S_2_TXD22: U$45.56, U$46.56
GP43_I2S_2_TXD23: U$47.56, U$48.56
GP43_I2S_2_TXD24: U$49.56, U$50.56
GP43_I2S_2_TXD25: U$51.56, U$52.56
GP43_I2S_2_TXD26: U$53.56, U$54.56
GP43_I2S_2_TXD27: U$55.56, U$56.56
GP43_I2S_2_TXD28: U$57.56, U$58.56
GP43_I2S_2_TXD29: U$59.56, U$60.56
GP43_I2S_2_TXD30: U$61.56, U$62.56
GP43_I2S_2_TXD31: U$63.56, U$64.56
GP44: U$2.24, U$3.24
GP45: U$2.26, U$3.26
GP46: U$2.28, U$3.28
GP47: U$2.30, U$3.30
GP48: U$2.32, U$3.32
GP49: U$2.34, U$3.34
GP50: U$11.28, U$12.28
GP51: U$11.26, U$12.26
GP52: U$11.25, U$12.25
GP53: U$11.24, U$12.24
GP54: U$13.48, U$14.48
GP55: U$13.42, U$14.42
GP56: U$13.34, U$14.34
GP57: U$13.32, U$14.32
GP58: U$13.30, U$14.30
GP59: U$13.28, U$14.28
GP60: U$13.26, U$14.26
GP61: U$13.25, U$14.25
GP62: U$13.24, U$14.24
GP63: U$15.48, U$16.48
GP64: U$15.42, U$16.42
GP65: U$15.34, U$16.34
GP66: U$15.32, U$16.32
GP67: U$15.30, U$16.30
GP68: U$15.28, U$16.28
GP69: U$15.26, U$16.26
GP70: U$15.25, U$16.25
GP71: U$15.24, U$16.24
GP72: U$17.48, U$18.48
GP73: U$17.42, U$18.42
GP74: U$17.34, U$18.34
GP75: U$17.32, U$18.32
GP76: U$17.30, U$18.30
GP77: U$17.28, U$18.28
GP77_SD_0_CD#: U$2.60, U$3.60
GP77_SD_0_CD#1: U$1.60, U$4.60
GP77_SD_0_CD#2: U$5.60, U$6.60
GP77_SD_0_CD#3: U$7.60, U$8.60
GP77_SD_0_CD#4: U$9.60, U$10.60
GP77_SD_0_CD#5: U$11.60, U$12.60
GP77_SD_0_CD#6: U$13.60, U$14.60
GP77_SD_0_CD#7: U$15.60, U$16.60
GP77_SD_0_CD#8: U$17.60, U$18.60
GP77_SD_0_CD#9: U$19.60, U$20.60
GP77_SD_0_CD#10: U$21.60, U$22.60
GP77_SD_0_CD#11: U$23.60, U$24.60
GP77_SD_0_CD#12: U$25.60, U$26.60
GP77_SD_0_CD#13: U$27.60, U$28.60
GP77_SD_0_CD#14: U$29.60, U$30.60
GP77_SD_0_CD#15: U$31.60, U$32.60
GP77_SD_0_CD#16: U$33.60, U$34.60
GP77_SD_0_CD#17: U$35.60, U$36.60
GP77_SD_0_CD#18: U$37.60, U$38.60
GP77_SD_0_CD#19: U$39.60, U$40.60
GP77_SD_0_CD#20: U$41.60, U$42.60
GP77_SD_0_CD#21: U$43.60, U$44.60
GP77_SD_0_CD#22: U$45.60, U$46.60
GP77_SD_0_CD#23: U$47.60, U$48.60
GP77_SD_0_CD#24: U$49.60, U$50.60
GP77_SD_0_CD#25: U$51.60, U$52.60
GP77_SD_0_CD#26: U$53.60, U$54.60
GP77_SD_0_CD#27: U$55.60, U$56.60
GP77_SD_0_CD#28: U$57.60, U$58.60
GP77_SD_0_CD#29: U$59.60, U$60.60
GP77_SD_0_CD#30: U$61.60, U$62.60
GP77_SD_0_CD#31: U$63.60, U$64.60
GP78: U$17.26, U$18.26
GP78_SD_0_CLK: U$2.58, U$3.58
GP78_SD_0_CLK1: U$1.58, U$4.58
GP78_SD_0_CLK2: U$5.58, U$6.58
GP78_SD_0_CLK3: U$7.58, U$8.58
GP78_SD_0_CLK4: U$9.58, U$10.58
GP78_SD_0_CLK5: U$11.58, U$12.58
GP78_SD_0_CLK6: U$13.58, U$14.58
GP78_SD_0_CLK7: U$15.58, U$16.58
GP78_SD_0_CLK8: U$17.58, U$18.58
GP78_SD_0_CLK9: U$19.58, U$20.58
GP78_SD_0_CLK10: U$21.58, U$22.58
GP78_SD_0_CLK11: U$23.58, U$24.58
GP78_SD_0_CLK12: U$25.58, U$26.58
GP78_SD_0_CLK13: U$27.58, U$28.58
GP78_SD_0_CLK14: U$29.58, U$30.58
GP78_SD_0_CLK15: U$31.58, U$32.58
GP78_SD_0_CLK16: U$33.58, U$34.58
GP78_SD_0_CLK17: U$35.58, U$36.58
GP78_SD_0_CLK18: U$37.58, U$38.58
GP78_SD_0_CLK19: U$39.58, U$40.58
GP78_SD_0_CLK20: U$41.58, U$42.58
GP78_SD_0_CLK21: U$43.58, U$44.58
GP78_SD_0_CLK22: U$45.58, U$46.58
GP78_SD_0_CLK23: U$47.58, U$48.58
GP78_SD_0_CLK24: U$49.58, U$50.58
GP78_SD_0_CLK25: U$51.58, U$52.58
GP78_SD_0_CLK26: U$53.58, U$54.58
GP78_SD_0_CLK27: U$55.58, U$56.58
GP78_SD_0_CLK28: U$57.58, U$58.58
GP78_SD_0_CLK29: U$59.58, U$60.58
GP78_SD_0_CLK30: U$61.58, U$62.58
GP78_SD_0_CLK31: U$63.58, U$64.58
GP79: U$17.25, U$18.25
GP79_SD_0_CMD: U$2.62, U$3.62
GP79_SD_0_CMD1: U$1.62, U$4.62
GP79_SD_0_CMD2: U$5.62, U$6.62
GP79_SD_0_CMD3: U$7.62, U$8.62
GP79_SD_0_CMD4: U$9.62, U$10.62
GP79_SD_0_CMD5: U$11.62, U$12.62
GP79_SD_0_CMD6: U$13.62, U$14.62
GP79_SD_0_CMD7: U$15.62, U$16.62
GP79_SD_0_CMD8: U$17.62, U$18.62
GP79_SD_0_CMD9: U$19.62, U$20.62
GP79_SD_0_CMD10: U$21.62, U$22.62
GP79_SD_0_CMD11: U$23.62, U$24.62
GP79_SD_0_CMD12: U$25.62, U$26.62
GP79_SD_0_CMD13: U$27.62, U$28.62
GP79_SD_0_CMD14: U$29.62, U$30.62
GP79_SD_0_CMD15: U$31.62, U$32.62
GP79_SD_0_CMD16: U$33.62, U$34.62
GP79_SD_0_CMD17: U$35.62, U$36.62
GP79_SD_0_CMD18: U$37.62, U$38.62
GP79_SD_0_CMD19: U$39.62, U$40.62
GP79_SD_0_CMD20: U$41.62, U$42.62
GP79_SD_0_CMD21: U$43.62, U$44.62
GP79_SD_0_CMD22: U$45.62, U$46.62
GP79_SD_0_CMD23: U$47.62, U$48.62
GP79_SD_0_CMD24: U$49.62, U$50.62
GP79_SD_0_CMD25: U$51.62, U$52.62
GP79_SD_0_CMD26: U$53.62, U$54.62
GP79_SD_0_CMD27: U$55.62, U$56.62
GP79_SD_0_CMD28: U$57.62, U$58.62
GP79_SD_0_CMD29: U$59.62, U$60.62
GP79_SD_0_CMD30: U$61.62, U$62.62
GP79_SD_0_CMD31: U$63.62, U$64.62
GP80: U$17.24, U$18.24
GP80_SD_0_DAT0: U$2.66, U$3.66
GP80_SD_0_DAT1: U$1.66, U$4.66
GP80_SD_0_DAT2: U$5.66, U$6.66
GP80_SD_0_DAT3: U$7.66, U$8.66
GP80_SD_0_DAT4: U$9.66, U$10.66
GP80_SD_0_DAT5: U$11.66, U$12.66
GP80_SD_0_DAT6: U$13.66, U$14.66
GP80_SD_0_DAT7: U$15.66, U$16.66
GP80_SD_0_DAT8: U$17.66, U$18.66
GP80_SD_0_DAT9: U$19.66, U$20.66
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
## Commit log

2014-08-11 initial commit ready for review
2014-08-12 removed Edzzanine from name
2014-09-19 corrected labels, added 3.3v regulator and corrected DCIN pin
2014-09-23 changed names of files
2014-09-25 repalced I2C resistors
2014-09-25 added bottom pour for VSYS
2014-10-17 Rev to 10, fix gnd/pwr/text
2014-10-17 fixed airwire with Package update
2014-10-17 removed stray Bplace from Package
2014-10-17 Ready for reds Tweak schematic, add value to regulator No known to-do items
2014-10-22 created panels
2014-12-03 Updated Readme.
2015-04-01 Updating README and production directory name
